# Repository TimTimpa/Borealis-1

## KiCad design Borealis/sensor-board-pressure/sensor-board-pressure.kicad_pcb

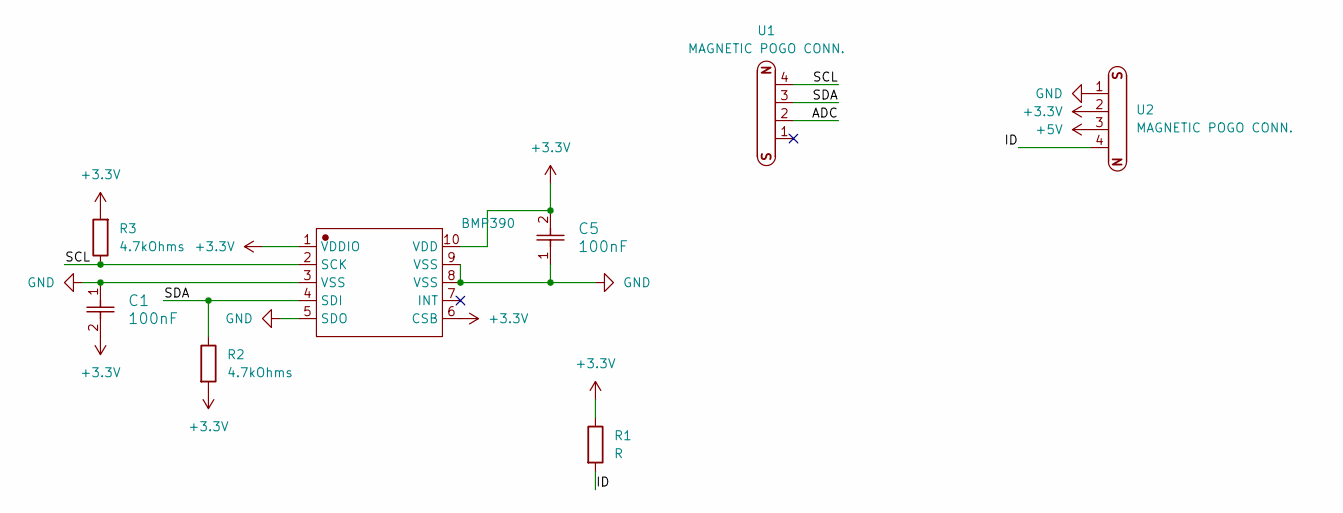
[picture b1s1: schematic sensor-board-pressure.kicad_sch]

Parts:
BMP390: BMP388
C1, C5: 100nF; C_0805_2012Metric
R1: R; R_0805_2012Metric
R2, R3: 4.7kOhms; R_0805_2012Metric
U1, U2: MAGNETIC POGO CONN.

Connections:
+3.3V: BMP390.1 (VDDIO), BMP390.6 (CSB), BMP390.10 (VDD), C1.2, C5.2, R1.1, R2.2, R3.2, U2.2
+5V: U2.3
/ADC: U1.2
/ID: R1.2, U2.4
/SCL: BMP390.2 (SCK), R3.1, U1.4
/SDA: BMP390.4 (SDI), R2.1, U1.3
GND: BMP390.3 (VSS), BMP390.5 (SDO), BMP390.8 (VSS), BMP390.9 (VSS), C1.1, C5.1, U2.1

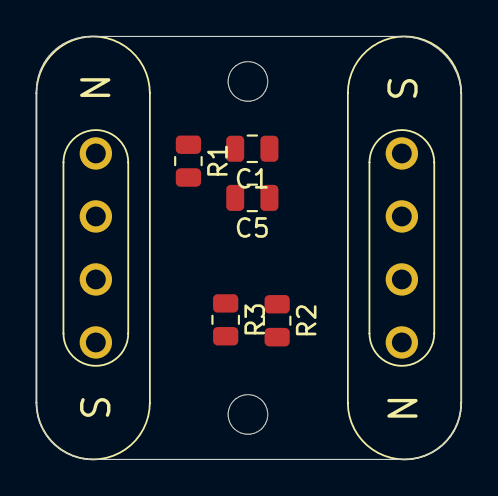
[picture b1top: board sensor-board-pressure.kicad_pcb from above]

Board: 2 copper layers, 23.6 x 23.5 mm, 8 parts (1 on the bottom side), 5 nets.

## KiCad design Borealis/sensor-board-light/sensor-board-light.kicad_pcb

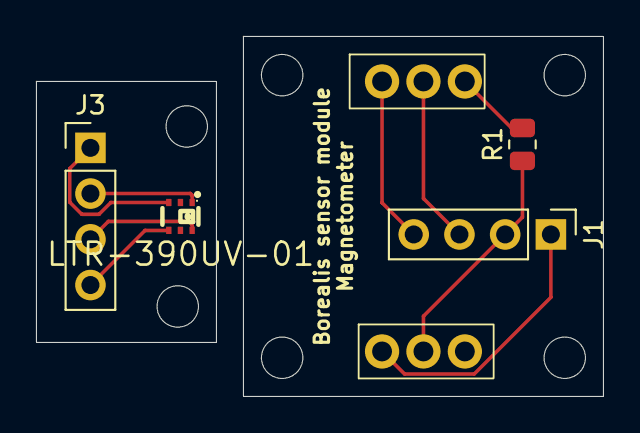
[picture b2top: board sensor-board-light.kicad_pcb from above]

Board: 2 copper layers, 31.5 x 20.0 mm, 6 parts (0 on the bottom side), 8 nets.

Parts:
J1, J3: Conn_01x04_Pin; PinHeader_1x04_P2.54mm_Vertical
J2: Conn_01x03_Pin (data connection to main board); 1x03 2.3 pitch
J5: Conn_01x03_Pin (power connection to main board); 1x03 2.3 pitch
LTR-390UV-01: SENSOR-SMD_LTR-390UV-01
R1: R; R_0805_2012Metric

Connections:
+3.3V: J1.2, J5.2, R1.1
/3.3v: J3.2, LTR-390UV-01.1 (VDD)
/ADC: J2.3, R1.2
/SCL: J1.4, J2.1
/SCL1: J3.4, LTR-390UV-01.4 (SCL)
/SDA: J1.3, J2.2
/SDA1: J3.3, LTR-390UV-01.6 (SDA)
GND: J1.1, J3.1, J5.1, LTR-390UV-01.3 (GND)

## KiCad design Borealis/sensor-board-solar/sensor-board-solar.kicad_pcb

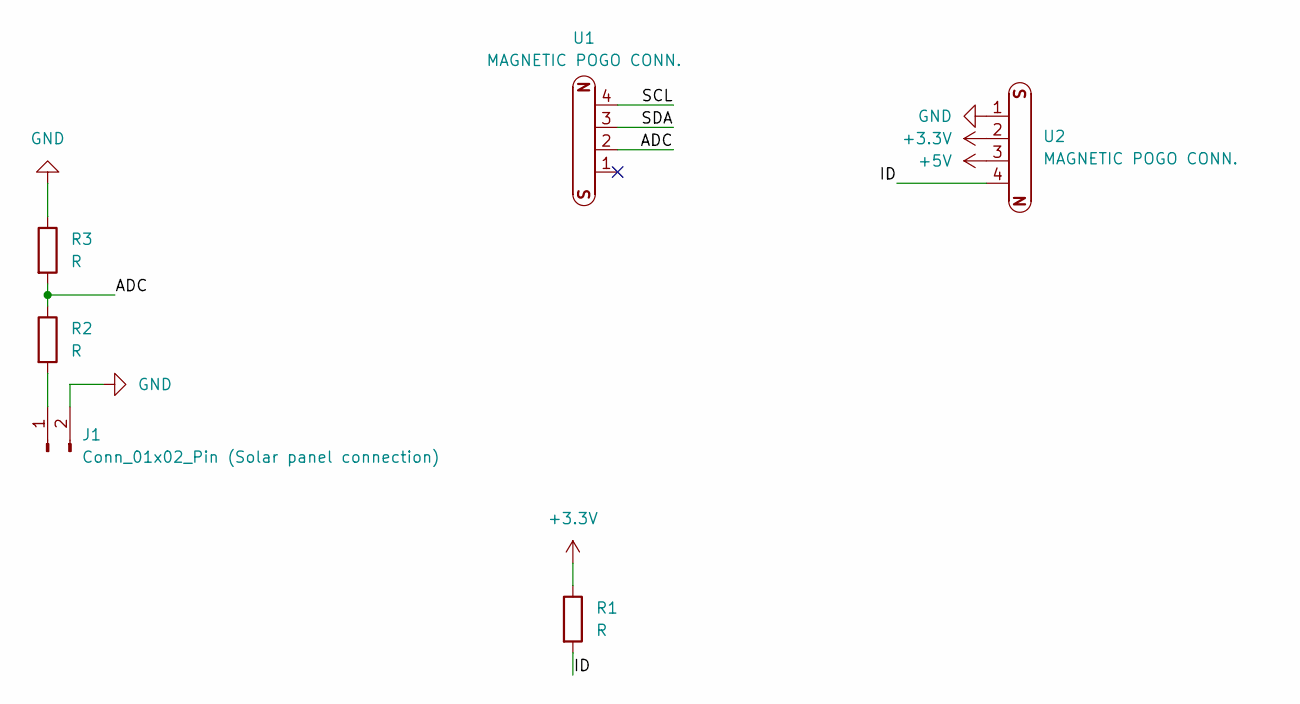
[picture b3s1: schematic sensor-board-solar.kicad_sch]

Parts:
J1: Conn_01x02_Pin (Solar panel connection); JST_PH_B2B-PH-K_1x02_P2.00mm_Vertical
R1, R2, R3: R; R_0805_2012Metric
U1, U2: MAGNETIC POGO CONN.

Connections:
+3.3V: R1.1, U2.2
+5V: U2.3
/ADC: R2.1, R3.2, U1.2
/ID: R1.2, U2.4
/SCL: U1.4
/SDA: U1.3
GND: J1.2, R3.1, U2.1
unnamed: J1.1, R2.2

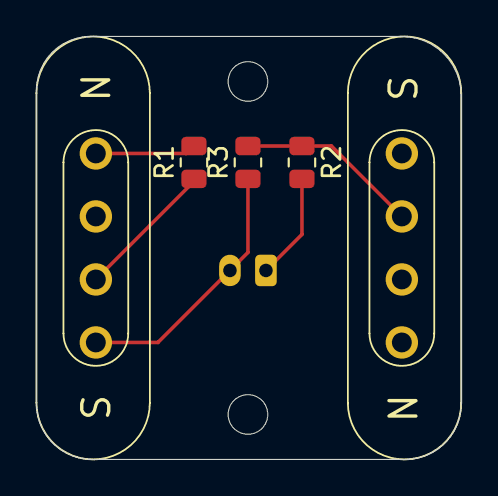
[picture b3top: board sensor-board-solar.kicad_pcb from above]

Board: 2 copper layers, 23.6 x 23.5 mm, 6 parts (1 on the bottom side), 5 nets.

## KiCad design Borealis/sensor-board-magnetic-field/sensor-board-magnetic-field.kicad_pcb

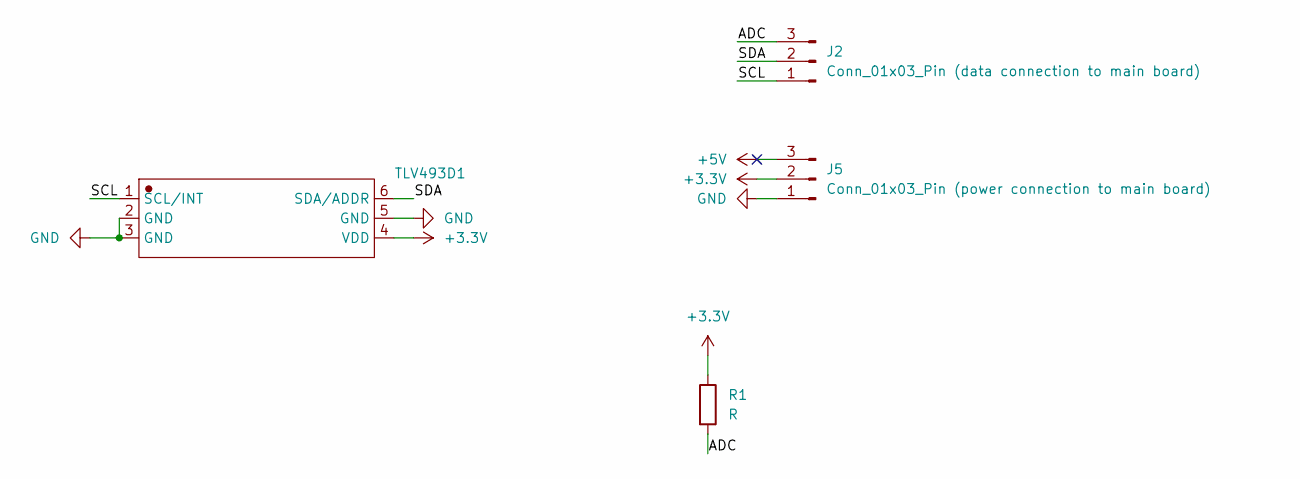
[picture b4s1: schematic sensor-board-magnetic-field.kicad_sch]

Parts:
J2: Conn_01x03_Pin (data connection to main board); 1x03 2.3 pitch
J5: Conn_01x03_Pin (power connection to main board); 1x03 2.3 pitch
R1: R; R_0805_2012Metric
TLV493D1: TLV493D

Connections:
+3.3V: J5.2, R1.1, TLV493D1.4 (VDD)
+5V: J5.3
/ADC: J2.3, R1.2
/SCL: J2.1, TLV493D1.1 (SCL/INT)
/SDA: J2.2, TLV493D1.6 (SDA/ADDR)
GND: J5.1, TLV493D1.2 (GND), TLV493D1.3 (GND), TLV493D1.5 (GND)

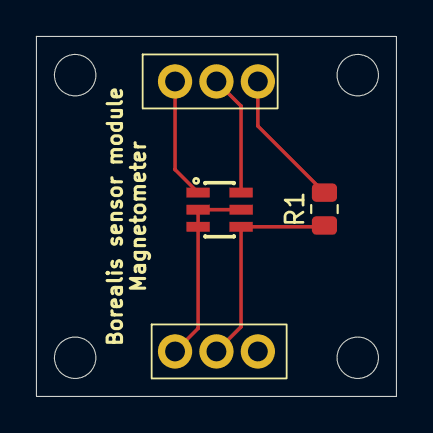
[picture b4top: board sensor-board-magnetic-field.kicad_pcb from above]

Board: 2 copper layers, 20.0 x 20.0 mm, 4 parts (0 on the bottom side), 5 nets.

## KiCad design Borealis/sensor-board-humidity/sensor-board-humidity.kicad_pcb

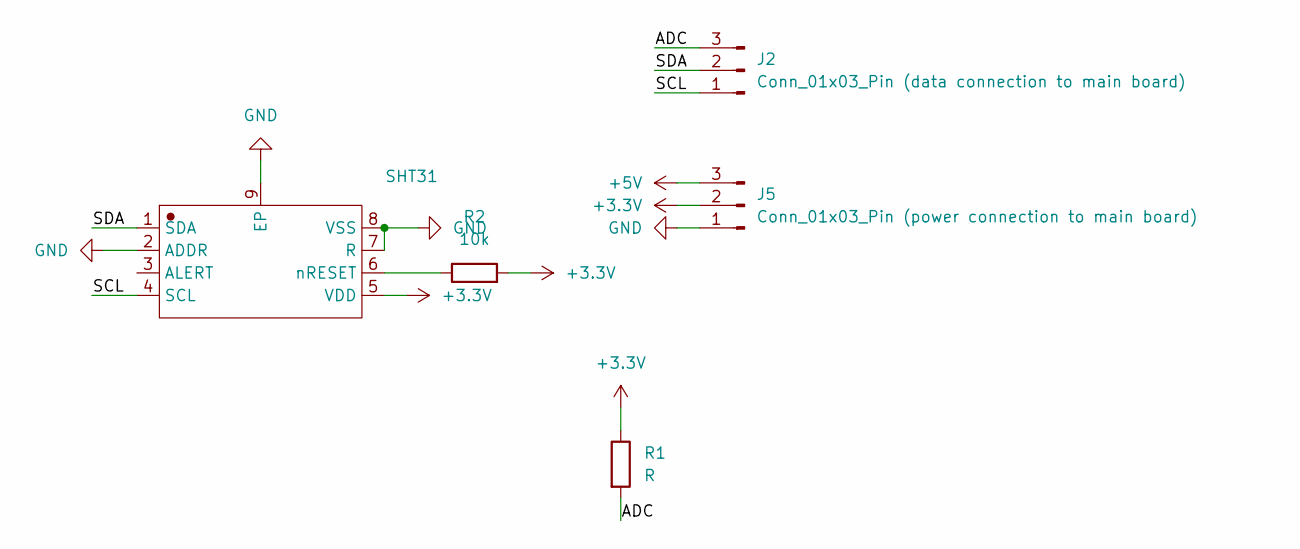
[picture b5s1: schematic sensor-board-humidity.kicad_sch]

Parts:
J2: Conn_01x03_Pin (data connection to main board); 1x03 2.3 pitch
J5: Conn_01x03_Pin (power connection to main board); 1x03 2.3 pitch
R1: R; R_0805_2012Metric
R2: 10k; R_0805_2012Metric
SHT31: sht31-footprint

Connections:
+3.3V: J5.2, R1.1, R2.2, SHT31.5 (VDD)
+5V: J5.3
/ADC: J2.3, R1.2
/SCL: J2.1, SHT31.4 (SCL)
/SDA: J2.2, SHT31.1 (SDA)
GND: J5.1, SHT31.2 (ADDR), SHT31.7 (R), SHT31.8 (VSS), SHT31.9 (EP)
unnamed: R2.1, SHT31.6 (nRESET)

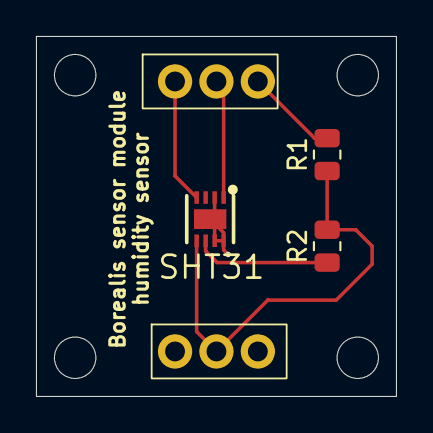
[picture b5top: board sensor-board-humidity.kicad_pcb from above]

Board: 2 copper layers, 20.0 x 20.0 mm, 5 parts (0 on the bottom side), 6 nets.

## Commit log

2025-11-15 Added mainboard files to Github
2025-12-06 Implement mainboard prototype for sensor logging
    This script initializes I2C and SPI interfaces for an OLED display and SD card, reads temperature and humidity data from sensors, and logs the data to a CSV file on the SD card while updating the dis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
2025-12-06 Add sensor logging and display functionality
    This script initializes I2C and SPI interfaces, reads sensor data, logs it to an SD card, and displays it on an OLED screen.
2025-12-06 Add timeset.py for setting DS3231 RTC time
2025-12-06 Implement SSD1306 OLED driver
    Added SSD1306 OLED driver with I2C and SPI support.
2025-12-06 Add SD card driver for SPI on MicroPython
2025-12-06 Create Wiring
2025-12-21 Remove Mainboard_prototype and update schematic
2025-12-21 Rename Borealis project to Borealis-mainboard
2025-12-21 Add Borealis control panel PCB project
2025-12-21 Update control panel schematic
2025-12-21 Added more boards
2025-12-21 added pico code and more boards
2025-12-21 Added a README file
2025-12-21 Create README with setup instructions for Pico
    Added setup guide and commands for Pico.
2025-12-22 Added error handling features
2025-12-23 fixed some stuff
2025-12-23 Added sensor board
2025-12-23 added solar sensor module
2025-12-23 stuff
2025-12-24 Changed main board based on what was discussed during the hardware meeting
2025-12-24 Create Data-analysis
2025-12-24 Create library
2025-12-24 Refactor numpy import for clarity and consistency
2025-12-26 Updating changes
2025-12-27 Added barometric sensor board
2025-12-28 Create module_swe
2025-12-28 Rename module_swe to data-analysis/module_swe
2025-12-28 Update and rename library.py to module_eng
2025-12-28 Update module_eng
2025-12-28 Update module_swe
2025-12-31 Rename module_eng to module_eng.py
2025-12-31 Rename module_swe to module_swe.py
2025-12-31 Create sample
2026-01-01 Create Motherboard
2026-01-01 Add files via upload
    Added SD Card Reader
2026-02-03 Added mainboard and temerature board
2026-02-03 Fixed a few things
2026-02-04 Rename Användarkod (1).ipynb to borealiskod.ipynb
2026-02-07 Worked on boards
2026-02-07 Worked on sum stuff
2026-03-07 Test
